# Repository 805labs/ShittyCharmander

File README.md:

# ShittyCharmander
Shitty Charmander Add-on badge for the Bender Badge

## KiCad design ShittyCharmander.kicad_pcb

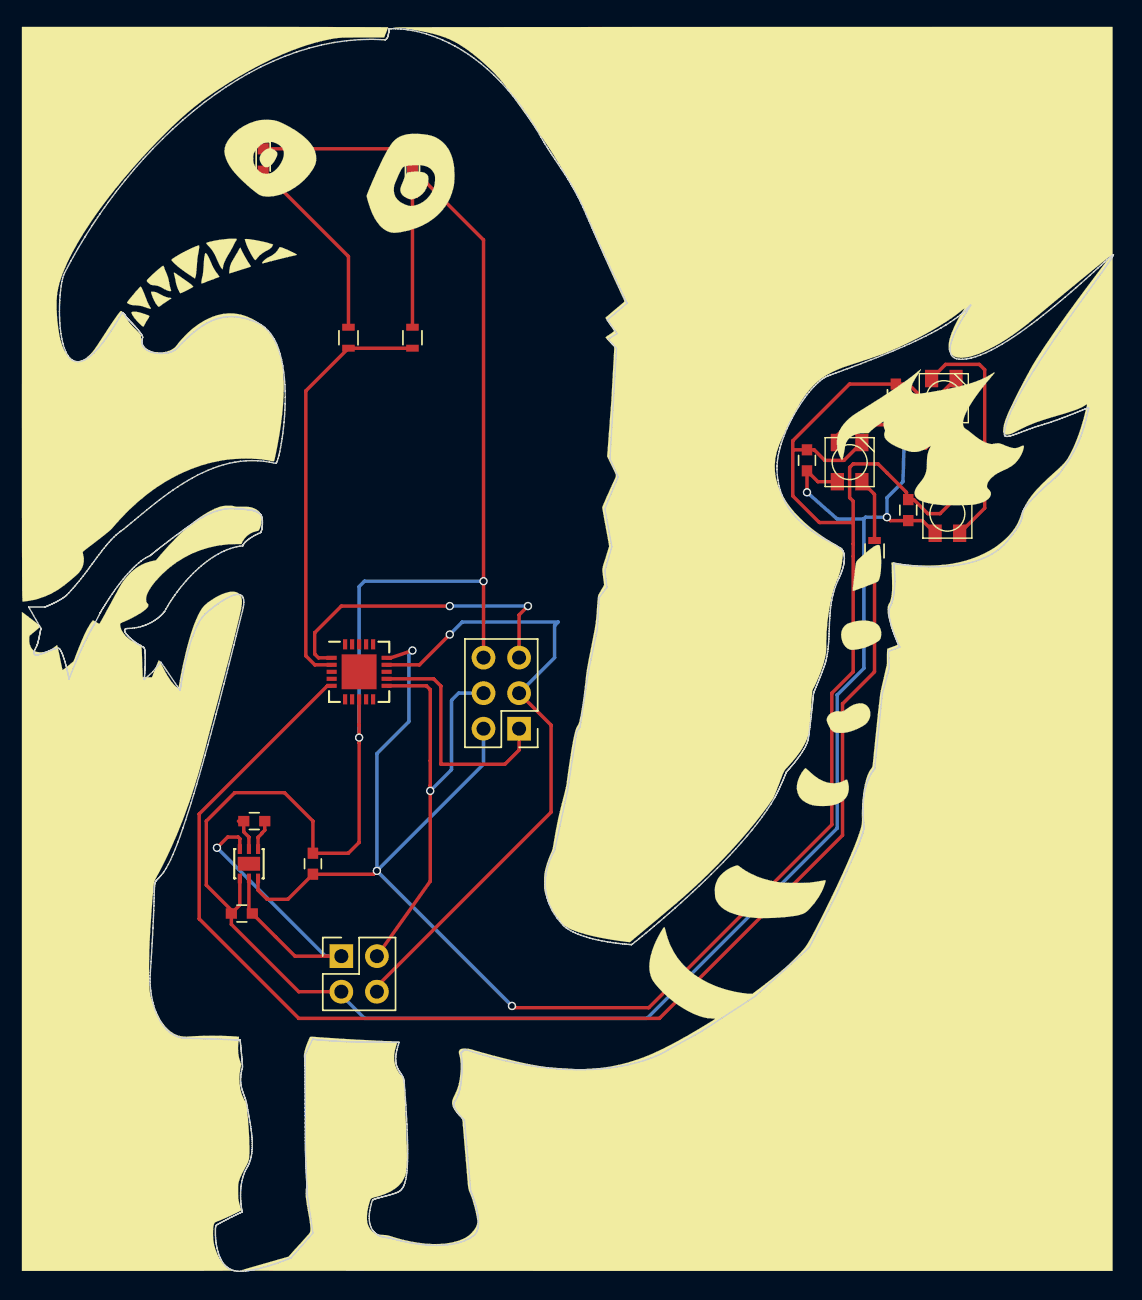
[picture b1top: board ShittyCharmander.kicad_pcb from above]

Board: 2 copper layers, 77.5 x 88.8 mm, 18 parts (0 on the bottom side), 16 nets.

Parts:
C1, C3: 2.2μF; C_0603
C2: 1μF; C_0603
C4, C5, C6: 0.1μF; C_0603
J1: Conn_02x02_Odd_Even; Pin_Header_Straight_2x02_Pitch2.54mm
J2: Conn_02x03_Odd_Even; Pin_Header_Straight_2x03_Pitch2.54mm
LED1, LED2: LED; LED_0603
LED3, LED4, LED5: WS2812B; SK6812-mini
R1, R2, R3: R; R_0603
U1: TPS60151; WSON-6_2x2mm_Pitch0.65mm
U2: ATTINY85-20MU; QFN-20-1EP_4x4mm_Pitch0.5mm

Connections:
3.3V: C2.1, J1.1, U1.2, U1.6
5V: C1.1, C4.1, C5.1, C6.1, J2.2, LED3.1, LED4.1, LED5.1, U1.3, U2.15
EYE_LEDS: R1.1, R2.1, U2.2
GND: C1.2, C2.2, C4.2, C5.2, C6.2, J1.3, J2.6, LED1.1, LED2.1, LED3.3, LED4.3, LED5.3, U1.1, U2.8
MISO: J2.1, U2.12
MOSI_SDA: J1.2, J2.4, U2.11
unnamed: C3.1, U1.5
unnamed: C3.2, U1.4
unnamed: LED1.2, R1.2
unnamed: LED2.2, R2.2
unnamed: LED3.4, LED4.2
unnamed: LED4.4, LED5.2
unnamed: LED5.4, R3.2
RESET: J2.5, U2.1
SCK_SCL: J1.4, J2.3, U2.14
TAIL_LEDS: R3.1, U2.5

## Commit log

2018-06-28 Added README
2018-06-28 Moved back silkscreen text to not intersect with vias
2018-07-01 Added clearance for arms for milling. Added gitignore
2018-07-01 Fixed ISP header footprint and corrected the traces to match the correct pinout
2018-07-01 Added updated schematic
